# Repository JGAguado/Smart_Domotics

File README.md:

[![License][license-shield]](LICENSE)

[![Project Maintenance][maintenance-shield]][maintenance]
[![BuyMeCoffee][buymecoffee-shield]][buymecoffee]

# Smart_Domotics

This repository contains the design files of the Smart_Domotics boards grouped by domotic application.

<ul>
   <li><a href="https://github.com/JGAguado/Smart_Lights">Smart Lights</a>: The Smart Lights is an ESP32 based board for controlling a dimmeable 12V led strip. Check out the branch for selecting between the X1 & the X4 versions, depending on the maximum dimeable outputs</li>

   <li><a href="https://github.com/JGAguado/Smart_Garden">Smart Garden</a>: The Smart Smart Garden provides an ESP32 based interface for controlling up to 4 relays. The output of the relays is a 24VAC or a selectable 5-24VDC power, mainly targeted to control sprinkles.</li>

   <li><a href="https://github.com/JGAguado/Smart_Alarm">Smart Alarm</a>: The Smart Alarm is an ESP32-CAM compatible board that integrates a PIR sensor and direct connection with a R503 fingerprint reader device.</li>

   <li><a href="https://github.com/JGAguado/Smart_Powermeter">Smart Powermeter</a>: The Smart Powermeter works as a shield for the TTGO T-Display allowing the measurement up to 6 CT clamps for reading electric current.</li>

   <li><a href="https://github.com/JGAguado/Smart_Herbs">Smart Herbs</a>: The Smart Herbs project is a set of PCBs compatible with the <a href="https://www.wmf.com/es/wmf-ambient-kraeuter-athome.html">WMF Ambient Pot</a> that provides a full smart solution for monitoring the plants. </li>

   <li><a href="https://github.com/JGAguado/Smart_Plant">Smart Plant</a>: The Smart Plant is a board that can be plugged directly on the soil, close to the plant, that allows the measurement of the environment (soil moisture, environment temperature & illuminance), and presents the information on an ePaper display.</li>

</ul>

## Project tree common for any board
---
<ul>
   <li>Design</li>
   <li>Documentation</li>

  <li><a href="./README.md">README.md</a></li>

</ul>

[license-shield]: https://img.shields.io/badge/License-CC%20BY--NC--SA%204.0-lightgrey.svg?style=for-the-badge

[maintenance-shield]: https://img.shields.io/badge/maintainer-J.%20G.%20Aguado-blue.svg?style=for-the-badge
[maintenance]: https://github.com/JGAguado

[buymecoffee-shield]: https://img.shields.io/badge/buy%20me%20a%20coffee-support-yellow.svg?style=for-the-badge
[buymecoffee]: https://www.buymeacoffee.com/J.G.Aguado

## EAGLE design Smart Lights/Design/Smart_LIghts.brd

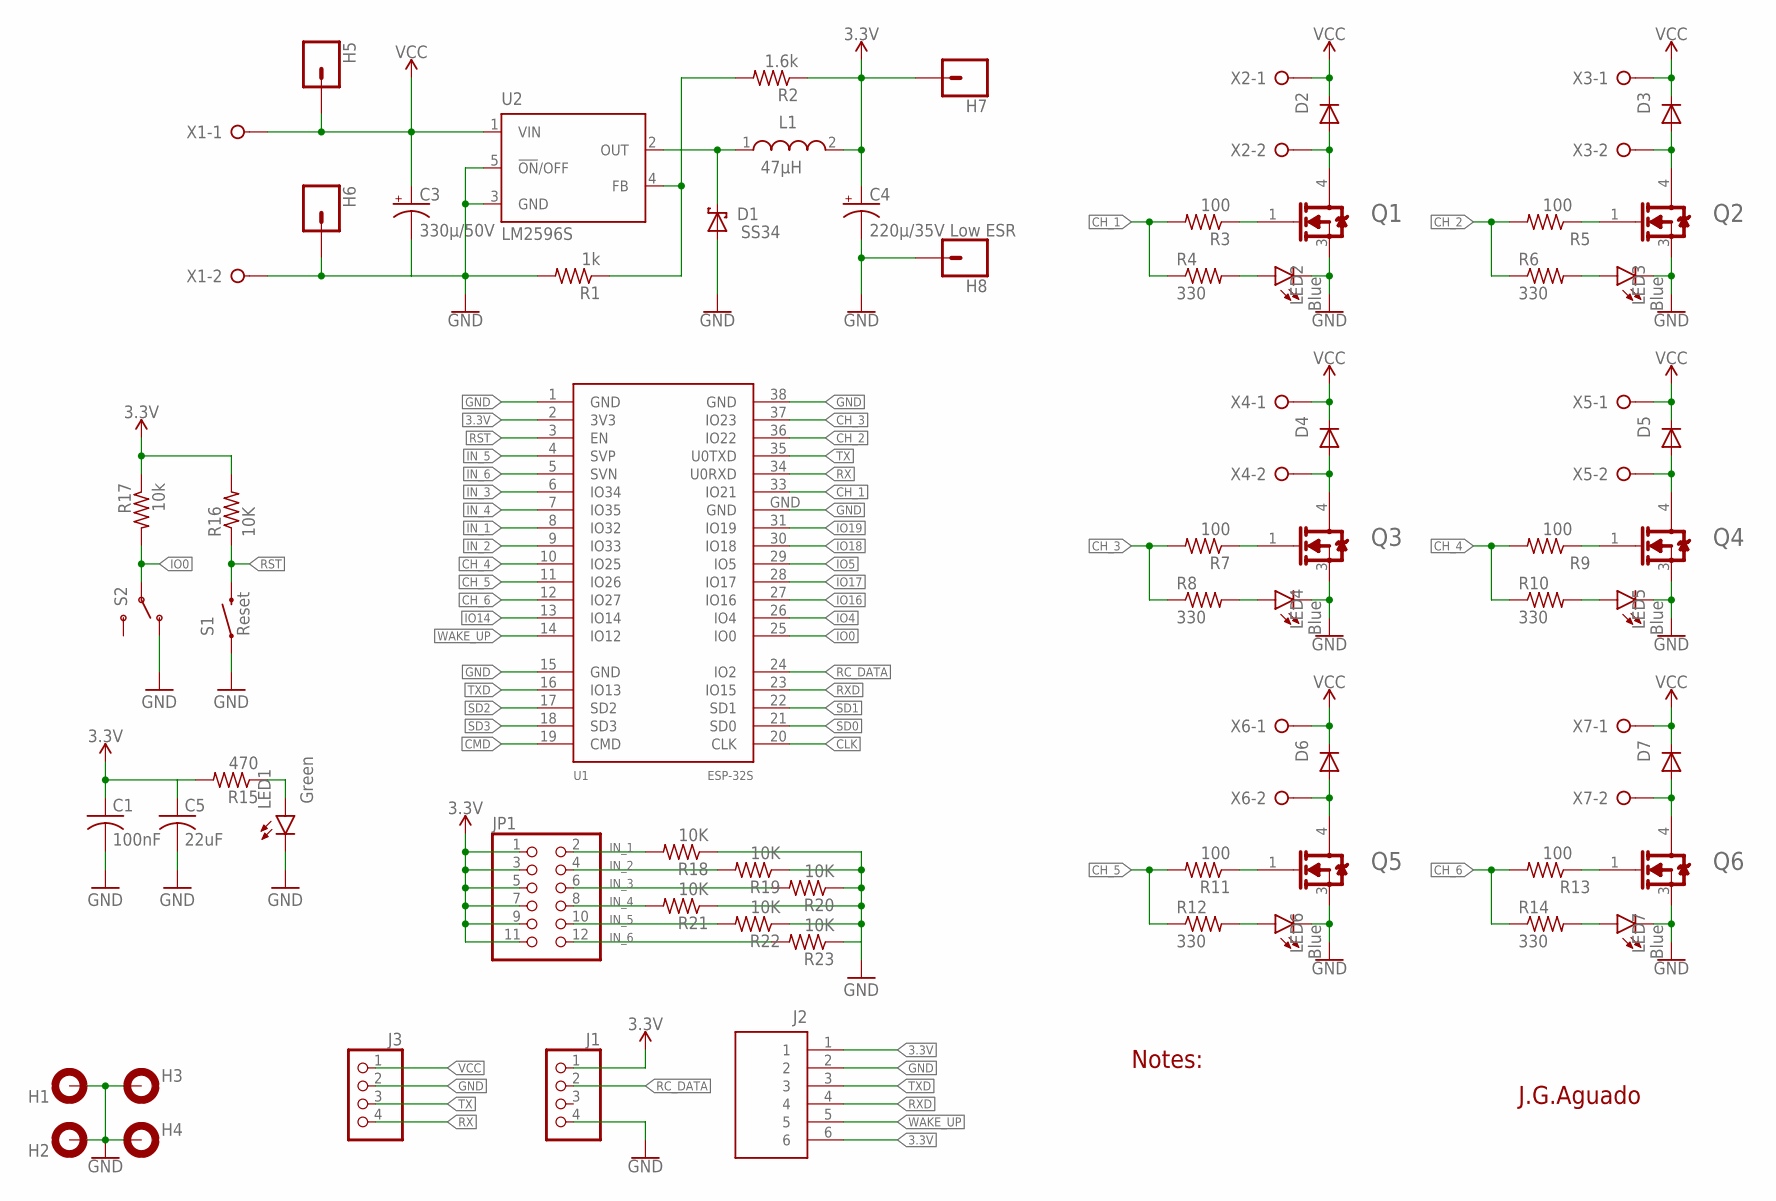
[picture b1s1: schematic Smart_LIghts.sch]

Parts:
C1: 100nF; C0603
C3: 330µ/50V; PANASONIC_F
C4: 220µ/35V Low ESR; PANASONIC_F
C5: 22uF; C0603
D1: SS34; SMB
D2, D3, D4, D5, D6, D7: DIODE-SOD123; SOD123
H1, H2, H3, H4: MOUNT-PAD-ROUND3.0; 3,0-PAD
H5, H6, H7, H8: CONN_01PTH_2MM; 1X01_2MM
J1, J3: PINHD-1X4; 1X04
J2: JST_6_PIN_VERTICAL; JST-6-SMD-VERT-1.0MM
JP1: PINHD-2X6; 2X06
L1: 47µH; WE-PD_1260/1245/1280/1210
LED1: Green; SML0603
LED2, LED3, LED4, LED5, LED6, LED7: Blue; SML0603
Q1, Q2, Q3, Q4, Q5, Q6: IRLR2905TRPBF; INFINEON_TECHNOLOGIES_IRLR2905TRPBF_0
R1: 1k; R0603
R2: 1.6k; R0603
R3, R5, R7, R9, R11, R13: 100; R0603
R4, R6, R8, R10, R12, R14: 330; R0603
R15: 470; R0603
R16, R18, R19, R20, R21, R22, R23: 10K; R0603
R17: 10k; R0603
S1: Reset; TACTILE_SWITCH_TALL
S2: SWITCH_SPDT; KPS-1290
U1: ESP-32S
U2: LM2596S; TO263-5
X1, X2, X3, X4, X5, X6, X7: W237-02P; W237-132

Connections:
3.3V: C1.1, C4.+, C5.1, H7.1, J1.1, J2.1, J2.6, JP1.1, JP1.3, JP1.5, JP1.7, JP1.9, JP1.11, L1.2, R2.1, R15.2, R16.2, R17.1, U1.2 (3V3)
CH_1: R3.2, R4.1, U1.33 (IO21)
CH_2: R5.2, R6.1, U1.36 (IO22)
CH_3: R7.2, R8.1, U1.37 (IO23)
CH_4: R9.2, R10.1, U1.10 (IO25)
CH_5: R11.2, R12.1, U1.11 (IO26)
CH_6: R13.2, R14.1, U1.12 (IO27)
CLK: U1.20 (CLK)
CMD: U1.19 (CMD)
GND: C1.2, C3.-, C4.-, C5.2, D1.A, H1.B3,0, H2.B3,0, H3.B3,0, H4.B3,0, H6.1, H8.1, J1.4, J2.2, J3.2, LED1.C, LED2.C, LED3.C, LED4.C, LED5.C, LED6.C, LED7.C, Q1.3 (SOURCE), Q2.3 (SOURCE), Q3.3 (SOURCE), Q4.3 (SOURCE), Q5.3 (SOURCE), Q6.3 (SOURCE), R1.2, R18.1, R19.1, R20.1, R21.1, R22.1, R23.1, S1.A2 (1), S2.O, U1.1 (GND), U1.15 (GND), U1.38 (GND), U1.GND, U2.3 (GND), U2.5 (!ON!/OFF), X1.2
IN_1: JP1.2, R18.2, U1.8 (IO32)
IN_2: JP1.4, R19.2, U1.9 (IO33)
IN_3: JP1.6, R20.2, U1.6 (IO34)
IN_4: JP1.8, R21.2, U1.7 (IO35)
IN_5: JP1.10, R22.2, U1.4 (SVP)
IN_6: JP1.12, R23.2, U1.5 (SVN)
IO0: R17.2, S2.P, U1.25 (IO0)
IO4: U1.26 (IO4)
IO5: U1.29 (IO5)
IO14: U1.13 (IO14)
IO16: U1.27 (IO16)
IO17: U1.28 (IO17)
IO18: U1.30 (IO18)
IO19: U1.31 (IO19)
unnamed: Q2.1 (GATE), R5.1
unnamed: D1.C, L1.1, U2.2 (OUT)
unnamed: R1.1, R2.2, U2.4 (FB)
unnamed: D2.A, Q1.4 (DRAIN), X2.2
unnamed: Q1.1 (GATE), R3.1
unnamed: D3.A, Q2.4 (DRAIN), X3.2
unnamed: Q3.1 (GATE), R7.1
unnamed: D4.A, Q3.4 (DRAIN), X4.2
unnamed: Q4.1 (GATE), R9.1
unnamed: D5.A, Q4.4 (DRAIN), X5.2
unnamed: Q5.1 (GATE), R11.1
unnamed: D6.A, Q5.4 (DRAIN), X6.2
unnamed: Q6.1 (GATE), R13.1
unnamed: D7.A, Q6.4 (DRAIN), X7.2
unnamed: LED1.A, R15.1
unnamed: LED4.A, R8.2
unnamed: LED2.A, R4.2
unnamed: LED3.A, R6.2
unnamed: LED5.A, R10.2
unnamed: LED6.A, R12.2
unnamed: LED7.A, R14.2
RC_DATA: J1.2, U1.24 (IO2)
RST: R16.1, S1.B2 (2), U1.3 (EN)
RX: J3.4, U1.34 (U0RXD)
RXD: J2.4, U1.23 (IO15)
SD0: U1.21 (SD0)
SD1: U1.22 (SD1)
SD2: U1.17 (SD2)
SD3: U1.18 (SD3)
TX: J3.3, U1.35 (U0TXD)
TXD: J2.3, U1.16 (IO13)
VCC: C3.+, D2.C, D3.C, D4.C, D5.C, D6.C, D7.C, H5.1, J3.1, U2.1 (VIN), X1.1, X2.1, X3.1, X4.1, X5.1, X6.1, X7.1
WAKE_UP: J2.5, U1.14 (IO12)

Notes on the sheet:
J.G.Aguado
Notes:

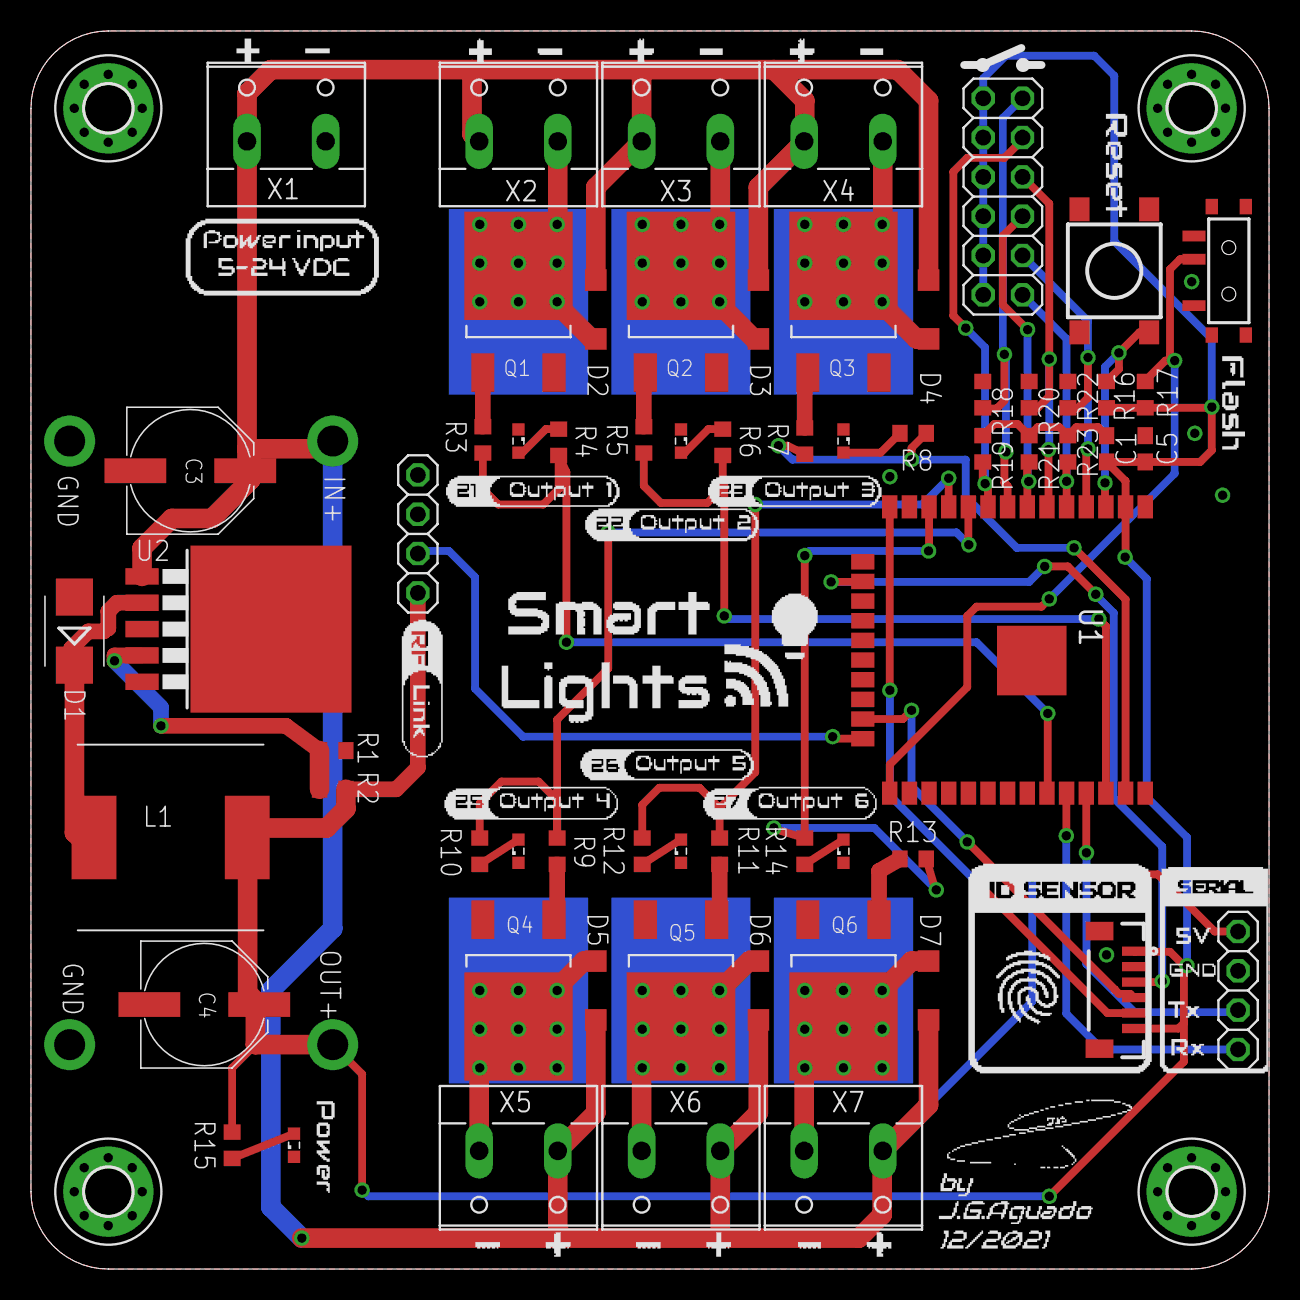
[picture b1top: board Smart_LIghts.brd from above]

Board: 2 copper layers, 80.0 x 80.0 mm, 71 parts (0 on the bottom side), 44 nets.

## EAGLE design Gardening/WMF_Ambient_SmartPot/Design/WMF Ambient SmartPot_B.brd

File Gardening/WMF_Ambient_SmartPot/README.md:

# WMF Ambient SmartPot
The WMF Ambient SmartPot project is a set of PCBs alternative to the original [WMF Ambient Pot](https://www.wmf.com/es/wmf-ambient-kraeuter-athome.html) that provides a full smart solution for monitoring the plants.

### Specifications:
 * ESP32 based (Bluetooth and Wifi functionalities)
 * Port for Neopixel LEDs
 * Support for 2 PWM driven pupms
 * Support for the original "touch" functionality
 * Support for the BME 280
 * Water level of the tank sensor
 * Wired probes support

### Applications:
Plug the Xiaomi Mi Flora on each pot and read the parameters provided via Bluetooth, or via the integrated ambient sensor BME 280. Push the parameters to a MQTT server or display the values throught the Neopixel LED array.

Set alerts when the temperatures drop or automatize watering tasks with the PWM support for 5V water pumps

### Repository Contents
-------------------
* **/Documentation** - Data sheets, schematics, illustrations (.pdf)
* **/Hardware** - All Eagle design files (.brd, .sch)
* **/Production** - Production gerber files 
* **/Silkscreen** - Silkscreen documentation (.ppt, .png)

## License Information
-------------------
<br /><span xmlns:dct="http://purl.org/dc/terms/" property="dct:title">Domotics</span> by <a xmlns:cc="http://creativecommons.org/ns#" href="https://github.com/SpaceDIY/Domotics" property="cc:attributionName" rel="cc:attributionURL">J.G.Aguado</a> is licensed under a <a rel="license" href="http://creativecommons.org/licenses/by-nc/4.0/">Creative Commons ShareAlike 4.0 International License</a>.

Distributed as-is; no warranty is given.

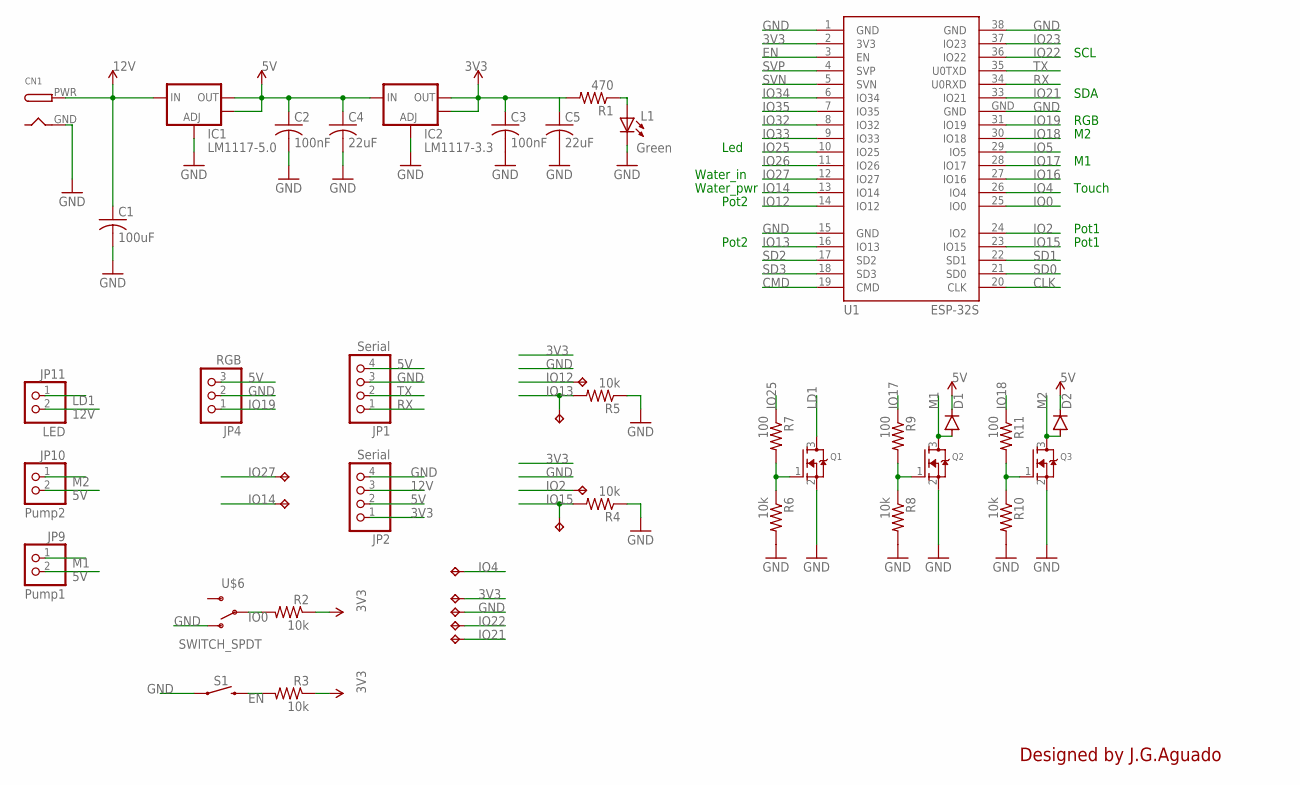
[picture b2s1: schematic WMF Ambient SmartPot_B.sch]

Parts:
C1: 100uF; 1206
C2, C3: 100nF; 1206
C4, C5: 22uF; 1206
CN1: DCBARREL-2; DCJACK_2MM_PTH-2
D1, D2: CGRM4002-G; SOD-123_MINI-SMA
IC1: LM1117-5.0; SOT223
IC2: LM1117-3.3; SOT223
JP1, JP2: Serial; 1X04
JP4: RGB; 1X03
JP9: Pump1; 1X02
JP10: Pump2; 1X02
JP11: LED; 1X02
L1: Green; LED1206
Q1, Q2, Q3: MOSFET-NREFLOW; SOT23
R1: 470; 1206
R2, R3, R4, R5, R6, R8, R10: 10k; 1206
R7, R9, R11: 100; 1206
S1: MOMENTARY-SWITCH-SPST-SMD-6.0X3.5MM; TACTILE_SWITCH_SMD_6.0X3.5MM
TP2, TP3, TP4, TP5, TP10, TP11, TP13, TP14, TP15, TP18, TP19: TPTP15SQ; TP15SQ
U1: ESP-32S
U$6: SWITCH_SPDT; KPS-1290

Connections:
3V3: C3.1, C5.1, IC2.2 (OUT), IC2.4 (OUT), JP2.1, R1.2, R2.1, R3.1, TP2.TP, U1.2 (3V3)
5V: C2.1, C4.1, D1.C, D2.C, IC1.2 (OUT), IC1.4 (OUT), IC2.3 (IN), JP1.4, JP2.2, JP4.3, JP9.2, JP10.2
12V: C1.1, CN1.PWR, IC1.3 (IN), JP2.3, JP11.2
CLK: U1.20 (CLK)
CMD: U1.19 (CMD)
EN: R3.2, S1.2, U1.3 (EN)
GND: C1.2, C2.2, C3.2, C4.2, C5.2, CN1.GND, IC1.1 (ADJ), IC2.1 (ADJ), JP1.3, JP2.4, JP4.2, L1.C, Q1.2 (S), Q2.2 (S), Q3.2 (S), R4.1, R5.1, R6.2, R8.2, R10.2, S1.1, TP3.TP, U1.1 (GND), U1.15 (GND), U1.38 (GND), U1.GND, U$6.O
IO0: R2.2, U1.25 (IO0), U$6.P
IO2: TP15.TP, U1.24 (IO2)
IO4: TP10.TP, U1.26 (IO4)
IO5: U1.29 (IO5)
IO12: TP14.TP, U1.14 (IO12)
IO13: R5.2, TP18.TP, U1.16 (IO13)
IO14: TP13.TP, U1.13 (IO14)
IO15: R4.2, TP19.TP, U1.23 (IO15)
IO16: U1.27 (IO16)
IO17: R9.1, U1.28 (IO17)
IO18: R11.1, U1.30 (IO18)
IO19: JP4.1, U1.31 (IO19)
IO21: TP5.TP, U1.33 (IO21)
IO22: TP4.TP, U1.36 (IO22)
IO23: U1.37 (IO23)
IO25: R7.1, U1.10 (IO25)
IO26: U1.11 (IO26)
IO27: TP11.TP, U1.12 (IO27)
IO32: U1.8 (IO32)
IO33: U1.9 (IO33)
IO34: U1.6 (IO34)
IO35: U1.7 (IO35)
LD1: JP11.1, Q1.3 (D)
M1: D1.A, JP9.1, Q2.3 (D)
M2: D2.A, JP10.1, Q3.3 (D)
unnamed: L1.A, R1.1
unnamed: Q1.1 (G), R6.1, R7.2
unnamed: Q2.1 (G), R8.1, R9.2
unnamed: Q3.1 (G), R10.1, R11.2
RX: JP1.1, U1.34 (U0RXD)
SD0: U1.21 (SD0)
SD1: U1.22 (SD1)
SD2: U1.17 (SD2)
SD3: U1.18 (SD3)
SVN: U1.5 (SVN)
SVP: U1.4 (SVP)
TX: JP1.2, U1.35 (U0TXD)

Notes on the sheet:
Designed by J.G.Aguado
SDA
SCL
RGB
Touch
Pot1
Pot2
Water_pwr
Water_in
Led

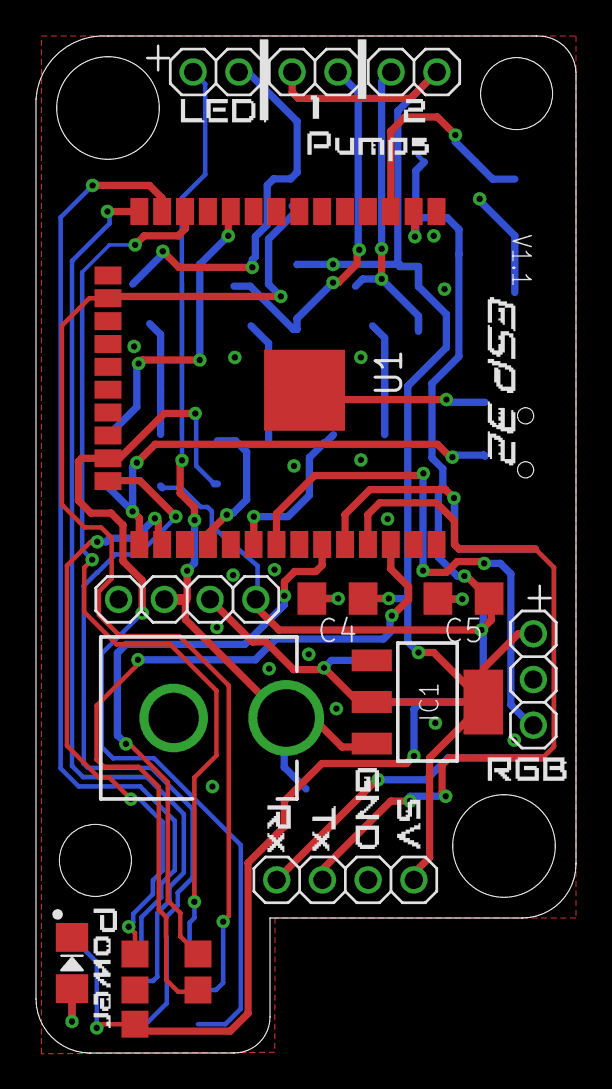
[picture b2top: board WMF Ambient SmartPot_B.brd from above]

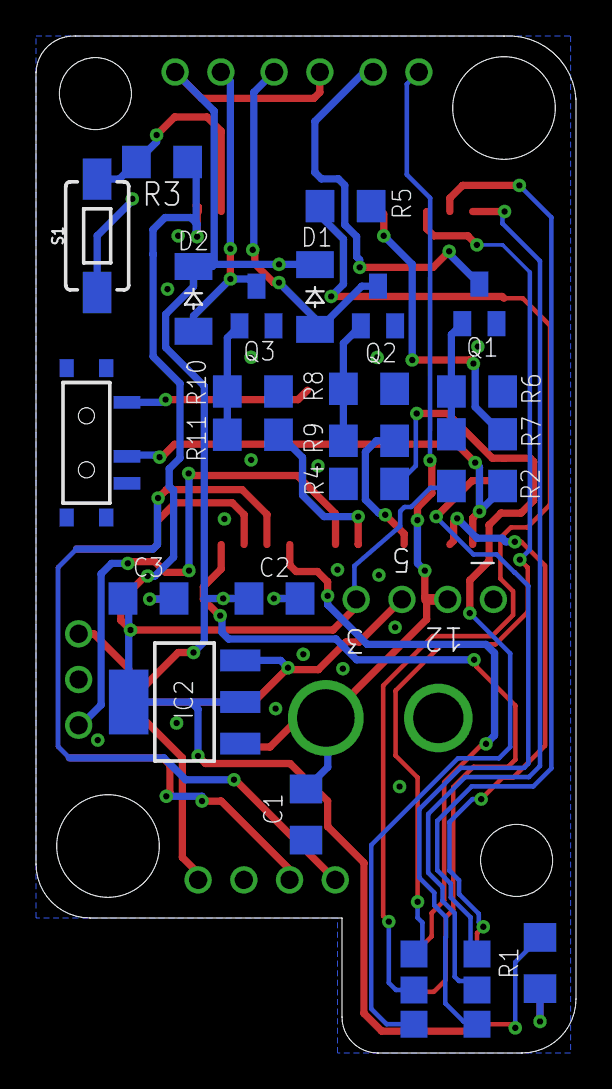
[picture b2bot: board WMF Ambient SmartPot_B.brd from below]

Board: 2 copper layers, 30.0 x 56.5 mm, 45 parts (28 on the bottom side), 28 nets.

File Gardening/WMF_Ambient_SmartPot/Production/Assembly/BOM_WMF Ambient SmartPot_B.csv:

"Part";"Value";"Device";"Package";"Description";"POPULARITY";"PROD_ID";"TP_SIGNAL_NAME";
"C1";"100uF";"C1206";"1206";"";"";"";"";
"C2";"100nF";"C1206";"1206";"";"";"";"";
"C3";"100nF";"C1206";"1206";"";"";"";"";
"C4";"22uF";"C1206";"1206";"";"";"";"";
"C5";"22uF";"C1206";"1206";"";"";"";"";
"CN1";"";"DCBARRELPTH";"DCJACK_2MM_PTH";"2.0mm DC Barrel Jack";"";"";"";
"D1";"CGRM4002-G";"CGRM4002-G";"SOD-123_MINI-SMA";"Molded plasitc,JEDEC SOD-123/Mini SMA";"0";"";"";
"D2";"CGRM4002-G";"CGRM4002-G";"SOD-123_MINI-SMA";"Molded plasitc,JEDEC SOD-123/Mini SMA";"0";"";"";
"IC1";"LM1117-5.0";"V_REG_LM1117SOT223";"SOT223";"Voltage Regulator LM1117";"";"";"";
"IC2";"LM1117-3.3";"V_REG_LM1117SOT223";"SOT223";"Voltage Regulator LM1117";"";"";"";
"JP1";"Serial";"PINHD-1X4";"1X04";"PIN HEADER";"";"";"";
"JP4";"RGB";"PINHD-1X3";"1X03";"PIN HEADER";"";"";"";
"JP5";"Pot1";"PINHD-1X4";"1X04";"PIN HEADER";"";"";"";
"JP6";"Pot2";"PINHD-1X4";"1X04";"PIN HEADER";"";"";"";
"JP8";"Water Tank";"PINHD-1X3";"1X03";"PIN HEADER";"";"";"";
"JP9";"Pump1";"PINHD-1X2";"1X02";"PIN HEADER";"";"";"";
"JP10";"Pump2";"PINHD-1X2";"1X02";"PIN HEADER";"";"";"";
"JP11";"LED";"PINHD-1X2";"1X02";"PIN HEADER";"";"";"";
"L1";"Green";"LED1206";"LED1206";"";"";"";"";
"Q1";"";"MOSFET-NREFLOW";"SOT23";"N-Channel Mosfet";"";"";"";
"Q2";"";"MOSFET-NREFLOW";"SOT23";"N-Channel Mosfet";"";"";"";
"Q3";"";"MOSFET-NREFLOW";"SOT23";"N-Channel Mosfet";"";"";"";
"R1";"470";"R1206";"1206";"";"";"";"";
"R2";"10k";"R1206";"1206";"";"";"";"";
"R4";"10k";"R1206";"1206";"";"";"";"";
"R5";"10k";"R1206";"1206";"";"";"";"";
"R6";"10k";"R1206";"1206";"";"";"";"";
"R7";"100";"R1206";"1206";"";"";"";"";
"R8";"10k";"R1206";"1206";"";"";"";"";
"R9";"100";"R1206";"1206";"";"";"";"";
"R10";"10k";"R1206";"1206";"";"";"";"";
"R11";"100";"R1206";"1206";"";"";"";"";
"TP2";"TPTP15SQ";"TPTP15SQ";"TP15SQ";"Test pad";"0";"";"";
"TP3";"TPTP15SQ";"TPTP15SQ";"TP15SQ";"Test pad";"0";"";"";
"TP4";"TPTP15SQ";"TPTP15SQ";"TP15SQ";"Test pad";"0";"";"";
"TP5";"TPTP15SQ";"TPTP15SQ";"TP15SQ";"Test pad";"0";"";"";
"TP10";"TPTP15SQ";"TPTP15SQ";"TP15SQ";"Test pad";"0";"";"";
"TP11";"TPTP15SQ";"TPTP15SQ";"TP15SQ";"Test pad";"0";"";"";
"TP13";"TPTP15SQ";"TPTP15SQ";"TP15SQ";"Test pad";"0";"";"";
"TP14";"TPTP15SQ";"TPTP15SQ";"TP15SQ";"Test pad";"0";"";"";
"TP15";"TPTP15SQ";"TPTP15SQ";"TP15SQ";"Test pad";"0";"";"";
"TP18";"TPTP15SQ";"TPTP15SQ";"TP15SQ";"Test pad";"0";"";"";
"TP19";"TPTP15SQ";"TPTP15SQ";"TP15SQ";"Test pad";"0";"";"";
"U$6";"SWITCH_SPDT";"SWITCH_SPDT";"KPS-1290";"SWCH-10651";"";"SWCH-10651";"";
"U1";"ESP-32S";"ESP-32S";"ESP-32S";"Ai-Thinker ESP-32S";"";"";"";

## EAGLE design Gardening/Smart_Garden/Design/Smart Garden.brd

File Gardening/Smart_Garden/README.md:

# Smart Garden
The Smart Garden project is the all-in-one solution for controlling the garden based on an ESP32. 

With the Smart Garden board you can read up to 4 different wired sensors or other Bluetooth based devices (such as the Xiaomi Mi Flora) and activate the water irrigators (electrovalves or water pumps) according to your own automations and routines!

### Specifications:
 * ESP32 based (Bluetooth and Wifi functionalities)
 * 220 VAC direct connection (no need for adaptors)
 * Inputs: 4 wired connections with 2 analog ports each 
 * Outputs: 4 relays with configurable output (24VAC, 9VDC, 5VCD or 3.3VDC)

### Applications:
Simple and efective solution for DIY Gardening installations based on the programable ESP32 chipset. Control any 24V AC electrovalve or smaller 5V DC water pumps just by configuring the switches onboard.

### Repository Contents
-------------------
* **/Documentation** - Data sheets, schematics, illustrations (.pdf)
* **/Hardware** - All Eagle design files (.brd, .sch)
* **/Production** - Production gerber files 
* **/Silkscreen** - Silkscreen documentation (.ppt, .png)

## License Information
-------------------
<br /><span xmlns:dct="http://purl.org/dc/terms/" property="dct:title">Domotics</span> by <a xmlns:cc="http://creativecommons.org/ns#" href="https://github.com/SpaceDIY/Domotics" property="cc:attributionName" rel="cc:attributionURL">J.G.Aguado</a> is licensed under a <a rel="license" href="http://creativecommons.org/licenses/by-nc/4.0/">Creative Commons ShareAlike 4.0 International License</a>.

Distributed as-is; no warranty is given.

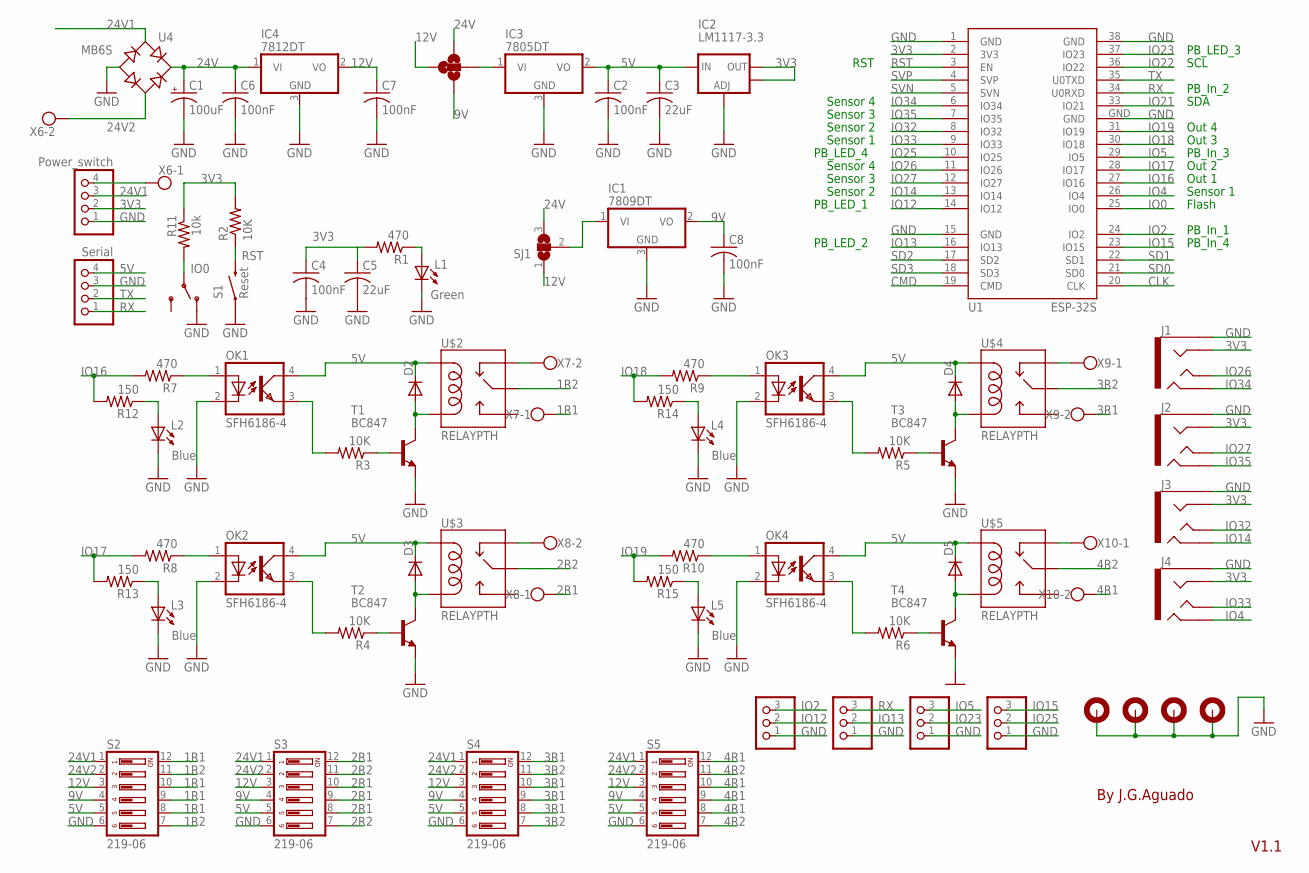
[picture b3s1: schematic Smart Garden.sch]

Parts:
C1: 100uF; D/7343-31R
C2, C4, C6, C7, C8: 100nF; 1206
C3, C5: 22uF; 1206
D2, D3, D4, D5: DIODE-SOD123; SOD123
H1, H2, H3, H4: MOUNT-PAD-ROUND3.0; 3,0-PAD
IC1: 7809DT; TO252
IC2: LM1117-3.3; SOT223
IC3: 7805DT; TO252
IC4: 7812DT; TO252
J1, J2, J3, J4: AUDIO_JACK_TRRSSMD_RA; AUDIO_JACK_3.5MM_TRRS_SMD_RA
JP1: Serial; 1X04
JP2, JP3, JP4, JP5: PINHD-1X3; 1X03
JP6: Power_switch; 1X04
L1: Green; LED1206
L2, L3, L4, L5: Blue; LED1206
OK1, OK2, OK3, OK4: SFH6186-4; SMD4-7
R1: 470; 1206
R2, R3, R4, R5, R6: 10K; R1206
R7, R8, R9, R10: 470; R1206
R11: 10k; 1206
R12, R13, R14, R15: 150; 1206
S1: Reset; TACTILE_SWITCH_TALL
S2, S3, S4, S5: 219-06; CTS-219-06
SJ1: SJ2W; SJ_2
SJ2: SJ3W; SJ_3_R
T1, T2, T3, T4: BC847; SOT23
U1: ESP-32S
U4: MB6S; SOIC-4
U$2, U$3, U$4, U$5: RELAYPTH; SRD-05VDC-SL-C
U$6: SWITCH_SPDT; KPS-1290
X6, X7, X8, X9, X10: W237-102

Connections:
1R1: S2.8, S2.9, S2.10, S2.12, X7.1
1R2: S2.7, S2.11, U$2.SWCOMMON
2R1: S3.8, S3.9, S3.10, S3.12, X8.1
2R2: S3.7, S3.11, U$3.SWCOMMON
3R1: S4.8, S4.9, S4.10, S4.12, X9.2
3R2: S4.7, S4.11, U$4.SWCOMMON
3V3: C4.1, C5.1, IC2.2 (OUT), IC2.4 (OUT), J1.RING1, J2.RING1, J3.RING1, J4.RING1, JP6.2, R1.2, R2.2, R11.1, U1.2 (3V3)
4R1: S5.8, S5.9, S5.10, S5.12, X10.2
4R2: S5.7, S5.11, U$5.SWCOMMON
5V: C2.1, C3.1, D2.C, D3.C, D4.C, D5.C, IC2.3 (IN), IC3.2 (VO), JP1.4, OK1.4 (COL), OK2.4 (COL), OK3.4 (COL), OK4.4 (COL), S2.5, S3.5, S4.5, S5.5, U$2.COIL1, U$3.COIL1, U$4.COIL1, U$5.COIL1
9V: C8.1, IC1.2 (VO), S2.4, S3.4, S4.4, S5.4, SJ2.P$2 (2)
12V: C7.1, IC4.2 (VO), S2.3, S3.3, S4.3, S5.3, SJ1.1, SJ2.P$4 (4)
24V: C1.+, C6.1, IC4.1 (VI), SJ1.3, SJ2.P$3 (3), U4.+
24V1: JP6.3, S2.1, S3.1, S4.1, S5.1, U4.~1 (AC1)
24V2: S2.2, S3.2, S4.2, S5.2, U4.~2 (AC2), X6.2
CLK: U1.20 (CLK)
CMD: U1.19 (CMD)
GND: C1.-, C2.2, C3.2, C4.2, C5.2, C6.2, C7.2, C8.2, H1.B3,0, H2.B3,0, H3.B3,0, H4.B3,0, IC1.3 (GND), IC2.1 (ADJ), IC3.3 (GND), IC4.3 (GND), J1.EARTH, J2.EARTH, J3.EARTH, J4.EARTH, JP1.3, JP2.1, JP3.1, JP4.1, JP5.1, JP6.1, L1.C, L2.C, L3.C, L4.C, L5.C, OK1.2 (C), OK2.2 (C), OK3.2 (C), OK4.2 (C), S1.A2 (1), S2.6, S3.6, S4.6, S5.6, T1.2 (E), T2.2 (E), T3.2 (E), T4.2 (E), U1.1 (GND), U1.15 (GND), U1.38 (GND), U1.GND, U4.-, U$6.O
IO0: R11.2, U1.25 (IO0), U$6.P
IO2: JP2.3, U1.24 (IO2)
IO4: J4.RING2, U1.26 (IO4)
IO5: JP4.3, U1.29 (IO5)
IO12: JP2.2, U1.14 (IO12)
IO13: JP3.2, U1.16 (IO13)
IO14: J3.RING2, U1.13 (IO14)
IO15: JP5.3, U1.23 (IO15)
IO16: R7.2, R12.2, U1.27 (IO16)
IO17: R8.2, R13.2, U1.28 (IO17)
IO18: R9.2, R14.2, U1.30 (IO18)
IO19: R10.2, R15.2, U1.31 (IO19)
IO21: U1.33 (IO21)
IO22: U1.36 (IO22)
IO23: JP4.2, U1.37 (IO23)
IO25: JP5.2, U1.10 (IO25)
IO26: J1.TIP, U1.11 (IO26)
IO27: J2.TIP, U1.12 (IO27)
IO32: J3.TIP, U1.8 (IO32)
IO33: J4.TIP, U1.9 (IO33)
IO34: J1.RING2, U1.6 (IO34)
IO35: J2.RING2, U1.7 (IO35)
unnamed: U$3.SWCLOSED (SWCLOSE), X8.2
unnamed: U$2.SWCLOSED (SWCLOSE), X7.2
unnamed: L1.A, R1.1
unnamed: U$4.SWCLOSED (SWCLOSE), X9.1
unnamed: U$5.SWCLOSED (SWCLOSE), X10.1
unnamed: JP6.4, X6.1
unnamed: D2.A, T1.3 (C), U$2.COIL0
unnamed: OK1.3 (EMIT), R3.2
unnamed: R3.1, T1.1 (B)
unnamed: D3.A, T2.3 (C), U$3.COIL0
unnamed: OK2.3 (EMIT), R4.2
unnamed: R4.1, T2.1 (B)
unnamed: D4.A, T3.3 (C), U$4.COIL0
unnamed: OK3.3 (EMIT), R5.2
unnamed: R5.1, T3.1 (B)
unnamed: D5.A, T4.3 (C), U$5.COIL0
unnamed: OK4.3 (EMIT), R6.2
unnamed: R6.1, T4.1 (B)
unnamed: OK1.1 (A), R7.1
unnamed: L2.A, R12.1
unnamed: L3.A, R13.1
unnamed: OK2.1 (A), R8.1
unnamed: L4.A, R14.1
unnamed: OK3.1 (A), R9.1
unnamed: L5.A, R15.1
unnamed: OK4.1 (A), R10.1
unnamed: IC1.1 (VI), SJ1.2
unnamed: IC3.1 (VI), SJ2.P$1 (1)
RST: R2.1, S1.B2 (2), U1.3 (EN)
RX: JP1.1, JP3.3, U1.34 (U0RXD)
SD0: U1.21 (SD0)
SD1: U1.22 (SD1)
SD2: U1.17 (SD2)
SD3: U1.18 (SD3)
SVN: U1.5 (SVN)
SVP: U1.4 (SVP)
TX: JP1.2, U1.35 (U0TXD)

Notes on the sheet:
Sensor 1
Sensor 2
Sensor 3
Sensor 4
Out 1
Out 2
Out 3
Out 4
Flash
SDA
SCL
PB_In_1
PB_LED_1
PB_In_2
PB_In_3
PB_In_4
PB_LED_4
PB_LED_3
PB_LED_2
RST
V1.1
By J.G.Aguado

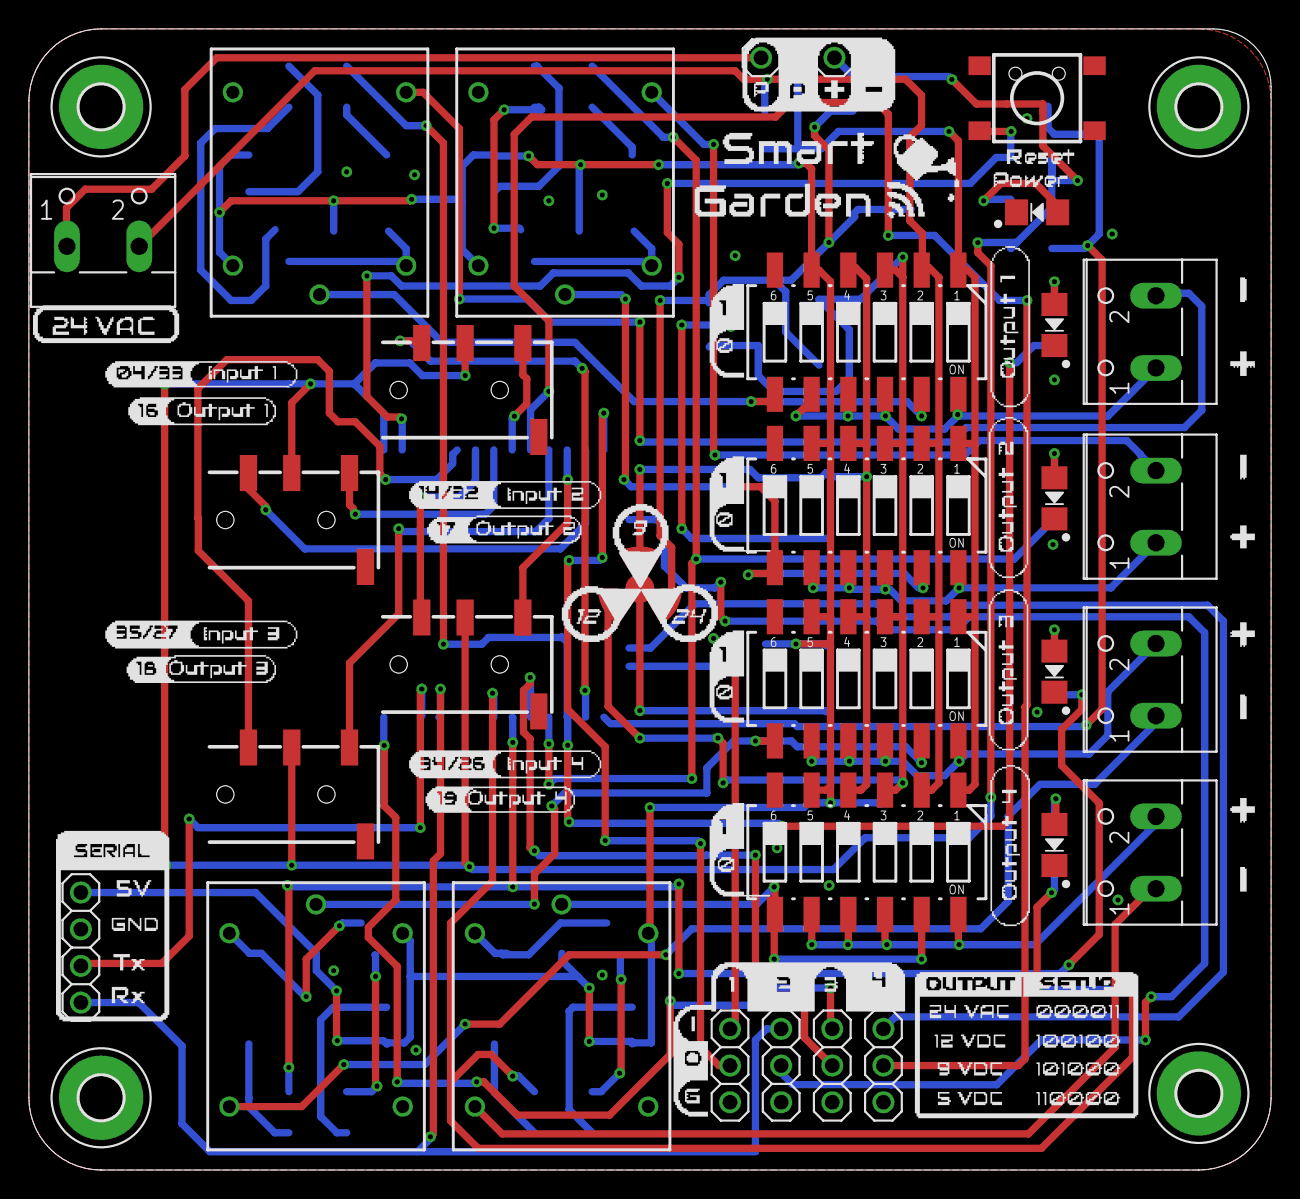
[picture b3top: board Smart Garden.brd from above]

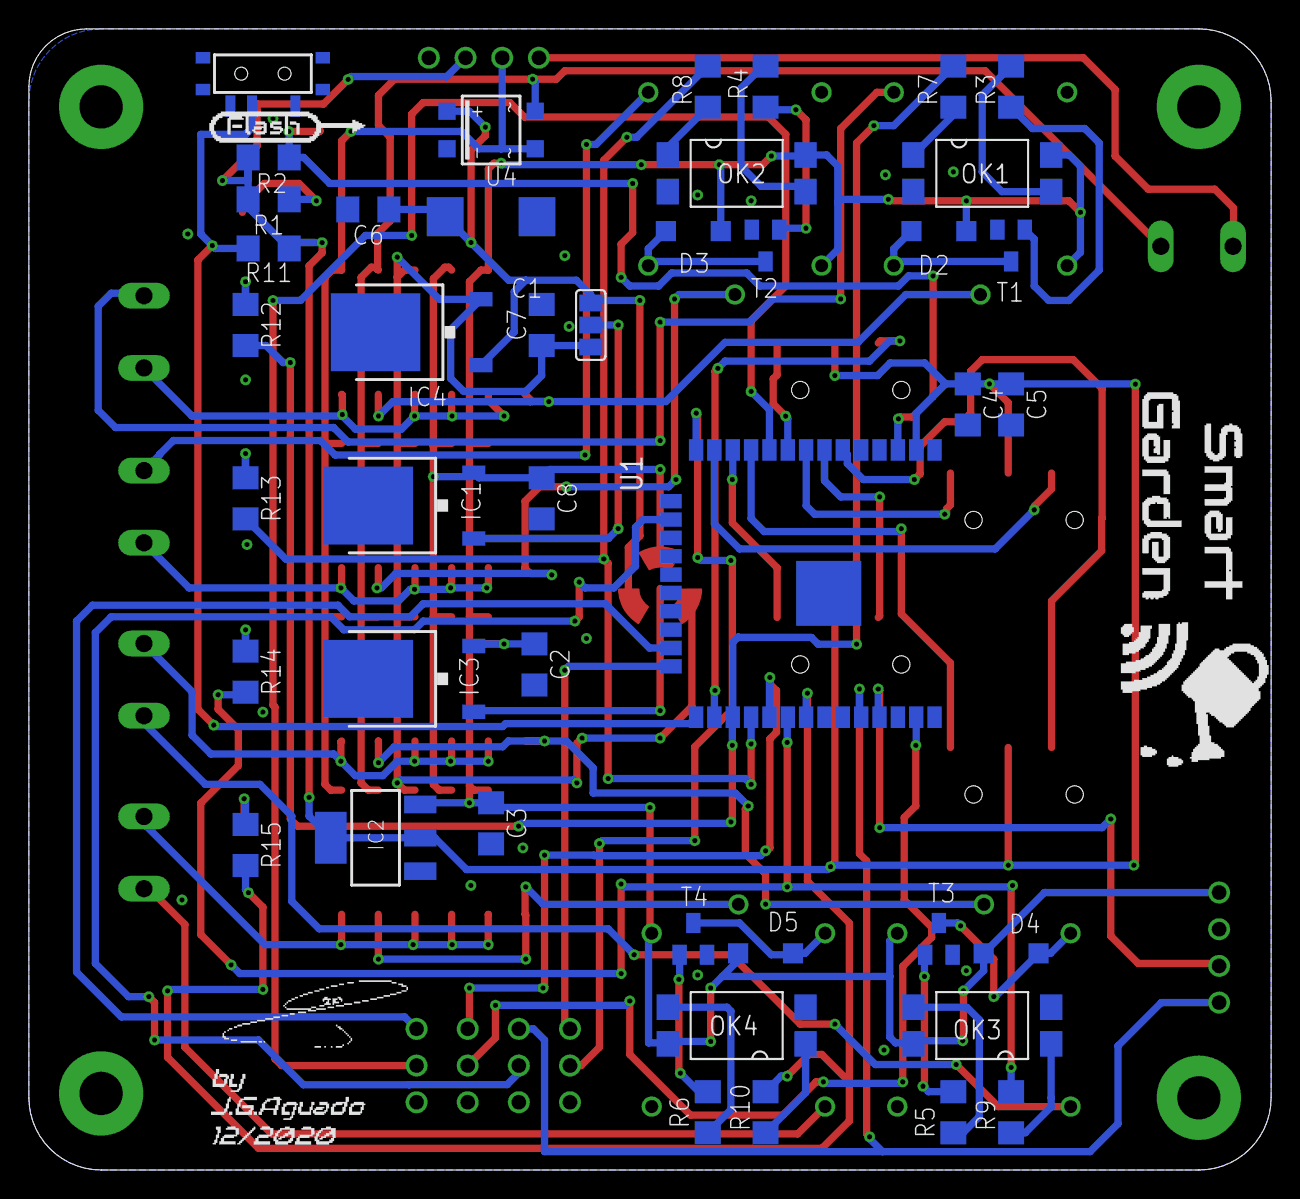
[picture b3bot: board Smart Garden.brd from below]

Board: 2 copper layers, 86.0 x 79.0 mm, 77 parts (43 on the bottom side), 67 nets.

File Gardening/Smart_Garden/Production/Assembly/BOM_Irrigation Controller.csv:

"Part";"Value";"Device";"Package";"Description";"MF";"MPN";"OC_FARNELL";"OC_NEWARK";"POPULARITY";"PROD_ID";"SF_ID";
"C1";"100uF";"CPOL-USCT7343";"CT7343";"POLARIZED CAPACITOR, American symbol";"";"";"";"";"";"";"";
"C2";"100nF";"C1206";"1206";"";"";"";"";"";"";"";"";
"C3";"22uF";"C1206";"1206";"";"";"";"";"";"";"";"";
"C4";"100nF";"C1206";"1206";"";"";"";"";"";"";"";"";
"C5";"22uF";"C1206";"1206";"";"";"";"";"";"";"";"";
"D1";"";"DIODE-SOD123";"SOD123";"DIODE";"";"";"";"";"";"";"";
"D2";"";"DIODE-SOD123";"SOD123";"DIODE";"";"";"";"";"";"";"";
"D3";"";"DIODE-SOD123";"SOD123";"DIODE";"";"";"";"";"";"";"";
"D4";"";"DIODE-SOD123";"SOD123";"DIODE";"";"";"";"";"";"";"";
"D5";"";"DIODE-SOD123";"SOD123";"DIODE";"";"";"";"";"";"";"";
"H1";"MOUNT-PAD-ROUND3.0";"MOUNT-PAD-ROUND3.0";"3,0-PAD";"MOUNTING PAD, round";"";"";"";"";"";"";"";
"H2";"MOUNT-PAD-ROUND3.0";"MOUNT-PAD-ROUND3.0";"3,0-PAD";"MOUNTING PAD, round";"";"";"";"";"";"";"";
"H3";"MOUNT-PAD-ROUND3.0";"MOUNT-PAD-ROUND3.0";"3,0-PAD";"MOUNTING PAD, round";"";"";"";"";"";"";"";
"H4";"MOUNT-PAD-ROUND3.0";"MOUNT-PAD-ROUND3.0";"3,0-PAD";"MOUNTING PAD, round";"";"";"";"";"";"";"";
"IC1";"7809DT";"7805DT";"TO252";"Positive VOLTAGE REGULATOR";"";"";"";"";"";"";"";
"IC2";"LM1117-3.3";"V_REG_LM1117SOT223";"SOT223";"Voltage Regulator LM1117";"";"";"";"";"";"";"";
"IC3";"7805DT";"7805DT";"TO252";"Positive VOLTAGE REGULATOR";"";"";"";"";"";"";"";
"J1";"AUDIO_JACK_TRRSSMD_RA";"AUDIO_JACK_TRRSSMD_RA";"AUDIO_JACK_3.5MM_TRRS_SMD_RA";"Audio Jack - 3.5mm TRRS (SMD)";"";"";"";"";"";"CONN-10676";"PRT-12639";
"J2";"AUDIO_JACK_TRRSSMD_RA";"AUDIO_JACK_TRRSSMD_RA";"AUDIO_JACK_3.5MM_TRRS_SMD_RA";"Audio Jack - 3.5mm TRRS (SMD)";"";"";"";"";"";"CONN-10676";"PRT-12639";
"J3";"AUDIO_JACK_TRRSSMD_RA";"AUDIO_JACK_TRRSSMD_RA";"AUDIO_JACK_3.5MM_TRRS_SMD_RA";"Audio Jack - 3.5mm TRRS (SMD)";"";"";"";"";"";"CONN-10676";"PRT-12639";
"J4";"AUDIO_JACK_TRRSSMD_RA";"AUDIO_JACK_TRRSSMD_RA";"AUDIO_JACK_3.5MM_TRRS_SMD_RA";"Audio Jack - 3.5mm TRRS (SMD)";"";"";"";"";"";"CONN-10676";"PRT-12639";
"JP1";"Serial";"PINHD-1X4";"1X04";"PIN HEADER";"";"";"";"";"";"";"";
"L1";"Green";"LED1206";"LED1206";"";"";"";"";"";"";"";"";
"L2";"Blue";"LED1206";"LED1206";"";"";"";"";"";"";"";"";
"L3";"Blue";"LED1206";"LED1206";"";"";"";"";"";"";"";"";
"L4";"Blue";"LED1206";"LED1206";"";"";"";"";"";"";"";"";
"L5";"Blue";"LED1206";"LED1206";"";"";"";"";"";"";"";"";
"OK1";"SFH6186-4";"SFH6186-4";"SMD4-7";"Optocoupler, Phototransistor Output, Low Input Current";"VISHAY/TELEFUNKEN";"SFH6186-4";"1469530";"21H7753";"";"";"";
"OK2";"SFH6186-4";"SFH6186-4";"SMD4-7";"Optocoupler, Phototransistor Output, Low Input Current";"VISHAY/TELEFUNKEN";"SFH6186-4";"1469530";"21H7753";"";"";"";
"OK3";"SFH6186-4";"SFH6186-4";"SMD4-7";"Optocoupler, Phototransistor Output, Low Input Current";"VISHAY/TELEFUNKEN";"SFH6186-4";"1469530";"21H7753";"";"";"";
"OK4";"SFH6186-4";"SFH6186-4";"SMD4-7";"Optocoupler, Phototransistor Output, Low Input Current";"VISHAY/TELEFUNKEN";"SFH6186-4";"1469530";"21H7753";"";"";"";
"R1";"470";"R1206";"1206";"";"";"";"";"";"";"";"";
"R2";"10K";"R-US_R1206";"R1206";"RESISTOR, American symbol";"";"";"";"";"";"";"";
"R3";"10K";"R-US_R1206";"R1206";"RESISTOR, American symbol";"";"";"";"";"";"";"";
"R4";"10K";"R-US_R1206";"R1206";"RESISTOR, American symbol";"";"";"";"";"";"";"";
"R5";"10K";"R-US_R1206";"R1206";"RESISTOR, American symbol";"";"";"";"";"";"";"";
"R6";"10K";"R-US_R1206";"R1206";"RESISTOR, American symbol";"";"";"";"";"";"";"";
"R7";"470";"R-US_R1206";"R1206";"RESISTOR, American symbol";"";"";"";"";"";"";"";
"R8";"470";"R-US_R1206";"R1206";"RESISTOR, American symbol";"";"";"";"";"";"";"";
"R9";"470";"R-US_R1206";"R1206";"RESISTOR, American symbol";"";"";"";"";"";"";"";
"R10";"470";"R-US_R1206";"R1206";"RESISTOR, American symbol";"";"";"";"";"";"";"";
"R11";"10k";"R1206";"1206";"";"";"";"";"";"";"";"";
"R12";"150";"R1206";"1206";"";"";"";"";"";"";"";"";
"R13";"150";"R1206";"1206";"";"";"";"";"";"";"";"";
"R14";"150";"R1206";"1206";"";"";"";"";"";"";"";"";
"R15";"150";"R1206";"1206";"";"";"";"";"";"";"";"";
"S1";"Reset";"SWITCH-MOMENTARY-2SMD-4";"TACTILE_SWITCH_TALL";"Various NO switches- pushbuttons, reed, etc";"";"";"";"";"";"";"";
"S2";"219-06";"219-06";"CTS-219-06";"Surface Mount DIP Switch Series 219 SMT";"";"";"unknown";"unknown";"";"";"";
"S3";"219-06";"219-06";"CTS-219-06";"Surface Mount DIP Switch Series 219 SMT";"";"";"unknown";"unknown";"";"";"";
"S4";"219-06";"219-06";"CTS-219-06";"Surface Mount DIP Switch Series 219 SMT";"";"";"unknown";"unknown";"";"";"";
"S5";"219-06";"219-06";"CTS-219-06";"Surface Mount DIP Switch Series 219 SMT";"";"";"unknown";"unknown";"";"";"";
"T1";"BC847";"BC847";"SOT23";"NPN TRANSISTOR";"";"";"";"";"5";"";"";
"T2";"BC847";"BC847";"SOT23";"NPN TRANSISTOR";"";"";"";"";"5";"";"";
"T3";"BC847";"BC847";"SOT23";"NPN TRANSISTOR";"";"";"";"";"5";"";"";
"T4";"BC847";"BC847";"SOT23";"NPN TRANSISTOR";"";"";"";"";"5";"";"";
"U$1";"TRANSFORMADOR_PE3010-M";"TRANSFORMADOR_PE3010-M";"TRANSFORMADOR_PE3010-M";"";"";"";"";"";"";"";"";
"U$2";"RELAYPTH";"RELAYPTH";"SRD-05VDC-SL-C";"SPDT relay (COM-00101)";"";"";"";"";"";"";"";
"U$3";"RELAYPTH";"RELAYPTH";"SRD-05VDC-SL-C";"SPDT relay (COM-00101)";"";"";"";"";"";"";"";
"U$4";"RELAYPTH";"RELAYPTH";"SRD-05VDC-SL-C";"SPDT relay (COM-00101)";"";"";"";"";"";"";"";
"U$5";"RELAYPTH";"RELAYPTH";"SRD-05VDC-SL-C";"SPDT relay (COM-00101)";"";"";"";"";"";"";"";
"U$6";"SWITCH_SPDT";"SWITCH_SPDT";"KPS-1290";"SWCH-10651";"";"";"";"";"";"SWCH-10651";"";
"U1";"ESP-32S";"ESP-32S";"ESP-32S";"Ai-Thinker ESP-32S";"";"";"";"";"";"";"";
"U4";"MB6S";"MB6S";"SOIC-4";"Bridge Rectifier";"";"";"";"";"";"";"";
"X1";"22-23-2021";"22-23-2021";"22-23-2021";".100" (2.54mm) Center Header - 2 Pin";"MOLEX";"22-23-2021";"1462926";"25C3832";"40";"";"";
"X2";"22-23-2021";"22-23-2021";"22-23-2021";".100" (2.54mm) Center Header - 2 Pin";"MOLEX";"22-23-2021";"1462926";"25C3832";"40";"";"";
"X3";"22-23-2021";"22-23-2021";"22-23-2021";".100" (2.54mm) Center Header - 2 Pin";"MOLEX";"22-23-2021";"1462926";"25C3832";"40";"";"";
"X4";"22-23-2021";"22-23-2021";"22-23-2021";".100" (2.54mm) Center Header - 2 Pin";"MOLEX";"22-23-2021";"1462926";"25C3832";"40";"";"";
"X5";"22-23-2021";"22-23-2021";"22-23-2021";".100" (2.54mm) Center Header - 2 Pin";"MOLEX";"22-23-2021";"1462926";"25C3832";"40";"";"";

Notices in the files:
parts and their libraries:
esp32: Creative Commons Attribution-ShareAlike 4.0 International
SparkFun-Retired: Licensing: Creative Commons ShareAlike 4.0 International - https://creativecommons.org/licenses/by-sa/4.0
SparkFun: Licensing: CC v3.0 Share-Alike You are welcome to use this library for commercial purposes.
